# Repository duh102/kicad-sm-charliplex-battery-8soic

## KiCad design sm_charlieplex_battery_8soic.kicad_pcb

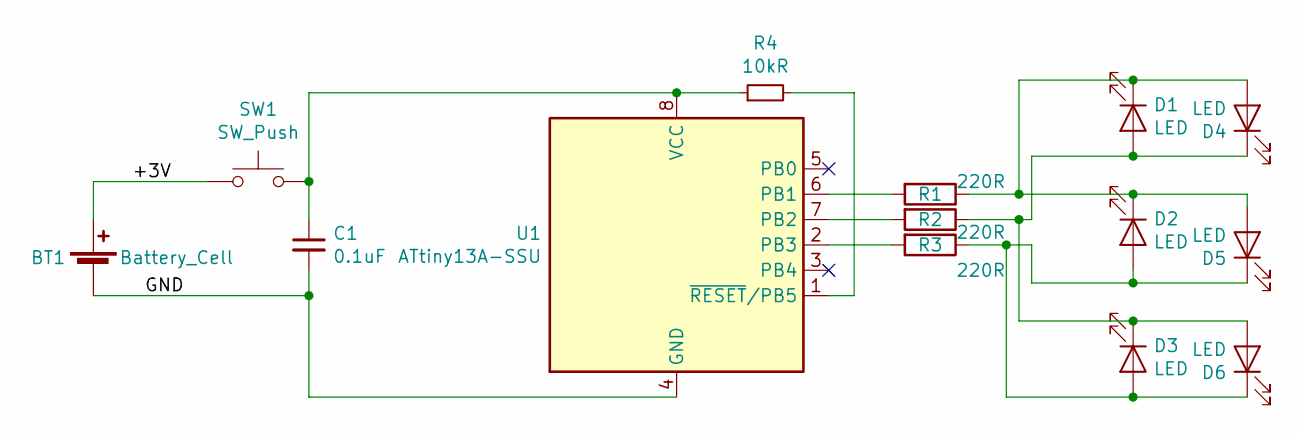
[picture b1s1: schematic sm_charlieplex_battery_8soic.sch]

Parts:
BT1: Battery_Cell; BatteryHolder_Keystone_2998_621_6.8x2.2mm
C1: 0.1uF; C_0805_2012Metric
D1, D2, D3, D4, D5, D6: LED; LED_0805_2012Metric
R1, R2, R3: 220R; R_0805_2012Metric
R4: 10kR; R_0805_2012Metric
SW1: SW_Push; SW_Push_2.6x1.6x0.53mm_EVP-BB2A9B000
U1: ATtiny13A-SSU; SOIC-8_3.9x4.9mm_P1.27mm

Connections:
/+3V: BT1.1 (+), SW1.1
/GND: BT1.2 (-), C1.2, U1.4 (GND)
unnamed: C1.1, R4.1, SW1.2, U1.8 (VCC)
unnamed: D1.1 (K), D2.1 (K), D4.2 (A), D5.2 (A), R1.1
unnamed: D1.2 (A), D3.1 (K), D4.1 (K), D6.2 (A), R2.1
unnamed: D2.2 (A), D3.2 (A), D5.1 (K), D6.1 (K), R3.1
unnamed: R1.2, U1.6 (PB1)
unnamed: R2.2, U1.7 (PB2)
unnamed: R3.2, U1.2 (PB3)
unnamed: R4.2, U1.1 (~RESET~/PB5)

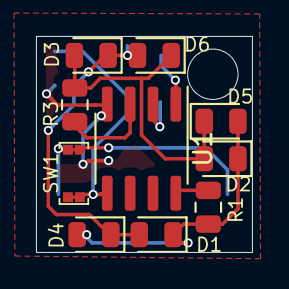
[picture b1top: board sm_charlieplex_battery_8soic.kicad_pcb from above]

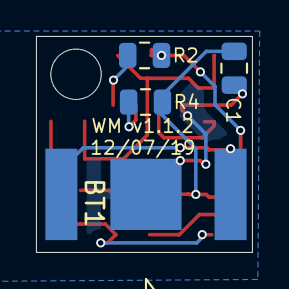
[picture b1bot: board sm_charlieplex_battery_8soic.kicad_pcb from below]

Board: 2 copper layers, 12.0 x 12.0 mm, 14 parts (4 on the bottom side), 10 nets.

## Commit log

2019-12-07 Initial seed commit
2019-12-07 Reformat to use ATTiny402
2020-12-09 Some changes
